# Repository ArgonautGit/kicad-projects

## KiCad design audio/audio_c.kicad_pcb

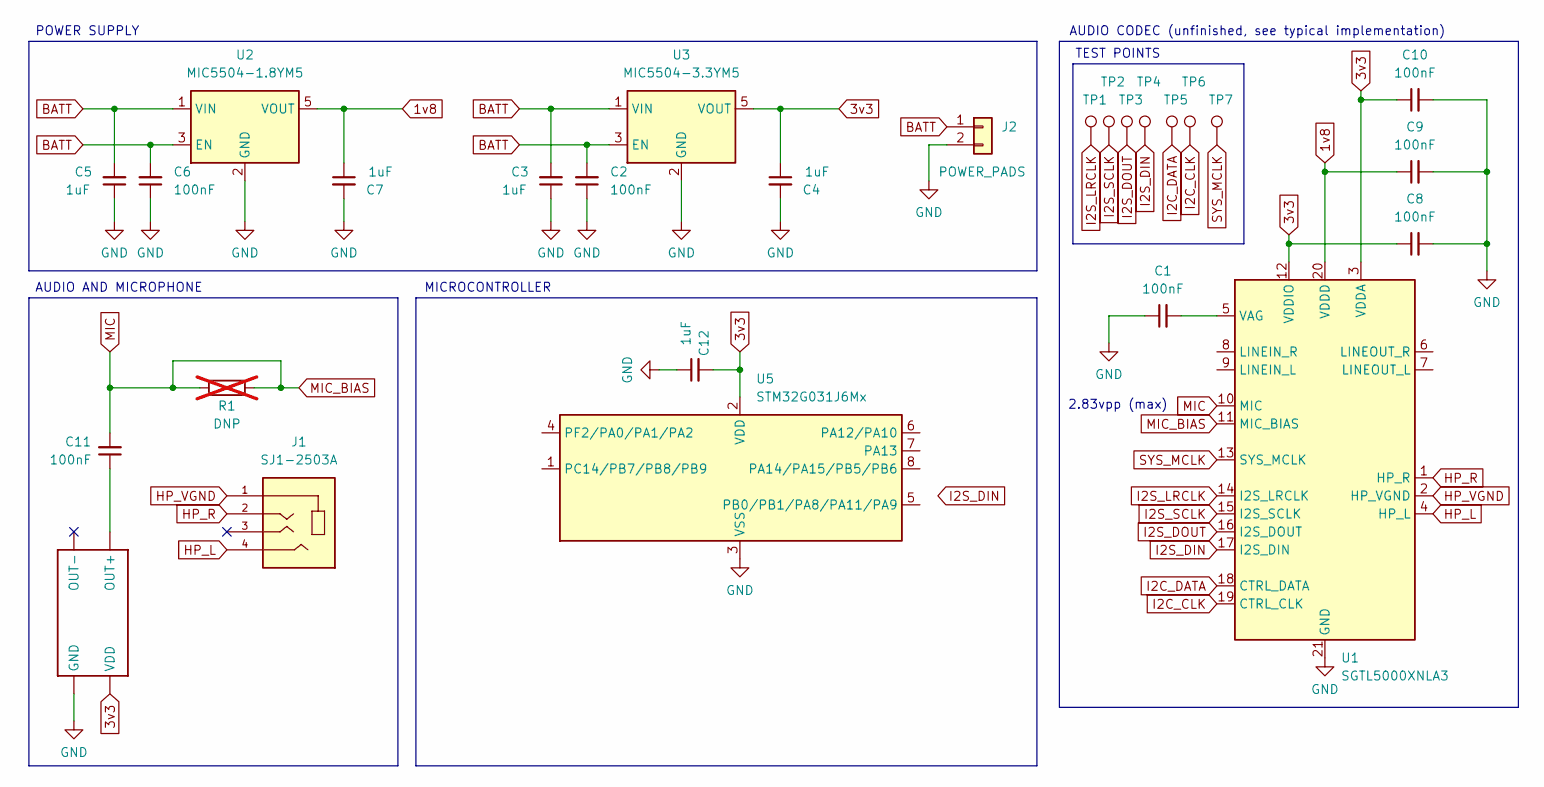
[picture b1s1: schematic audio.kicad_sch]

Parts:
C1, C2, C6, C8, C9, C10, C11: 100nF; C_0805_2012Metric_Pad1.18x1.45mm_HandSolder
C3, C4, C5, C7, C12: 1uF; C_0805_2012Metric_Pad1.18x1.45mm_HandSolder
J1: SJ1-2503A; CUI_SJ1-2503A
J2: POWER_PADS; test_2_pad
R1: DNP; R_1206_3216Metric_Pad1.30x1.75mm_HandSolder; not fitted
TP1, TP2, TP3, TP4, TP5, TP6, TP7: TestPoint; TestPoint_Pad_D1.0mm
U1: SGTL5000XNLA3; QFN-20-1EP_3x3mm_P0.4mm_EP1.65x1.65mm
U2: MIC5504-1.8YM5; SOT-23-5
U3: MIC5504-3.3YM5; SOT-23-5
U4: SPH8878LR5H-1
U5: STM32G031J6Mx; SOIC-8_3.9x4.9mm_P1.27mm

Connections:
1v8: C7.1, C9.1, U1.20 (VDDD), U2.5 (VOUT)
3v3: C4.1, C8.1, C10.1, C12.2, U1.3 (VDDA), U1.12 (VDDIO), U3.5 (VOUT), U4.5 (VDD), U5.2 (VDD)
BATT: C2.2, C3.2, C5.2, C6.2, J2.1, U2.1 (VIN), U2.3 (EN), U3.1 (VIN), U3.3 (EN)
GND: C1.1, C2.1, C3.1, C4.2, C5.1, C6.1, C7.2, C8.2, C9.2, C10.2, C12.1, J2.2, U1.21 (GND), U2.2 (GND), U3.2 (GND), U4.2 (GND), U4.3 (GND), U4.4 (GND), U5.3 (VSS)
HP_L: J1.4, U1.4 (HP_L)
HP_R: J1.2, U1.1 (HP_R)
HP_VGND: J1.1, U1.2 (HP_VGND)
I2C_CLK: TP6.1, U1.19 (CTRL_CLK), U5.5 (PB0/PB1/PA8/PA11/PA9)
I2C_DATA: TP5.1, U1.18 (CTRL_DATA), U5.6 (PA12/PA10)
I2S_DIN: TP4.1, U1.17 (I2S_DIN)
I2S_DOUT: TP3.1, U1.16 (I2S_DOUT)
I2S_LRCLK: TP1.1, U1.14 (I2S_LRCLK)
I2S_SCLK: TP2.1, U1.15 (I2S_SCLK)
MIC: C11.2, R1.1, R1.2, U1.10 (MIC), U1.11 (MIC_BIAS)
unnamed: C1.2, U1.5 (VAG)
unnamed: C11.1, U4.1 (OUT+)
SYS_MCLK: TP7.1, U1.13 (SYS_MCLK)

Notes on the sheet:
MICROCONTROLLER
TEST POINTS
AUDIO CODEC (unfinished, see typical implementation)
AUDIO AND MICROPHONE
2.83vpp (max)
POWER SUPPLY

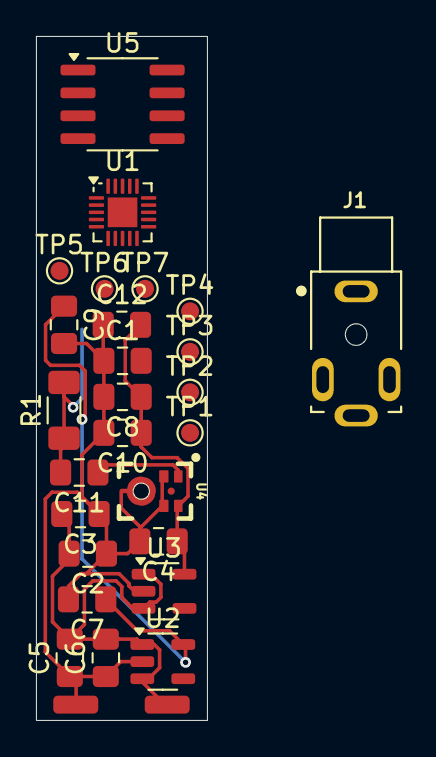
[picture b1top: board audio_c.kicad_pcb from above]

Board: 2 copper layers, 9.5 x 38.0 mm, 27 parts (0 on the bottom side), 17 nets.

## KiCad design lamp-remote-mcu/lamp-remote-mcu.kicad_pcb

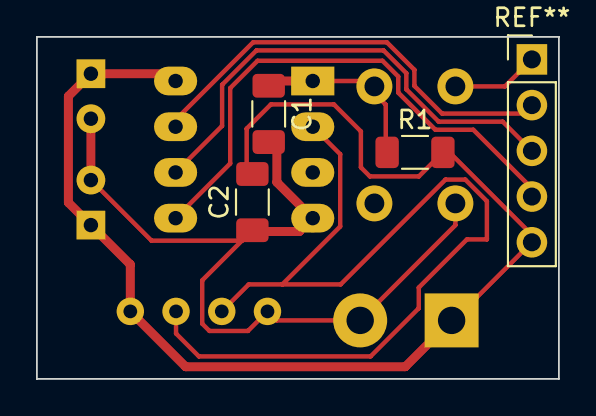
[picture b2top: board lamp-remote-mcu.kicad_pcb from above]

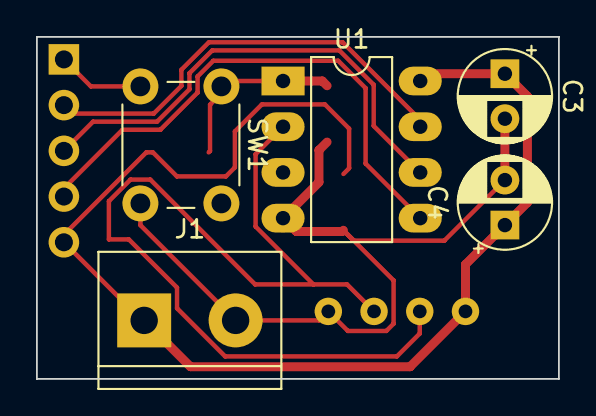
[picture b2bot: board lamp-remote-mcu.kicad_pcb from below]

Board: 2 copper layers, 29.0 x 19.0 mm, 9 parts (6 on the bottom side), 4 nets.

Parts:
C1, C2: 100nF; C_1206_3216Metric_Pad1.33x1.80mm_HandSolder
C3, C4: 10uF; CP_Radial_D5.0mm_P2.50mm
J1: SCREW TERMINAL; TerminalBlock_bornier-2_P5.08mm
J2: RX; rx
R1: 10k; R_1206_3216Metric_Pad1.30x1.75mm_HandSolder
SW1: SWITCH; SW_PUSH_6mm
U1: ATtiny13A-P; DIP-8_W7.62mm_LongPads

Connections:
GND: C1.2, C2.1, C3.2, C4.2, J1.2, J2.4, SW1.3 (B), U1.4 (GND)
unnamed: C1.1, R1.1, SW1.1 (A), U1.1 (~RESET/PB5)
RX: J2.2, J2.3, U1.2 (PB3)
VCC: C2.2, C3.1, C4.1, J1.1, J2.1, R1.2, U1.8 (VCC)
